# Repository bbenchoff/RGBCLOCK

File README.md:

# RGBCLOCK
RGB Seven-segment clock

On hackaday.io: http://hackaday.io/project/5156-rgb-seven-segment-clock

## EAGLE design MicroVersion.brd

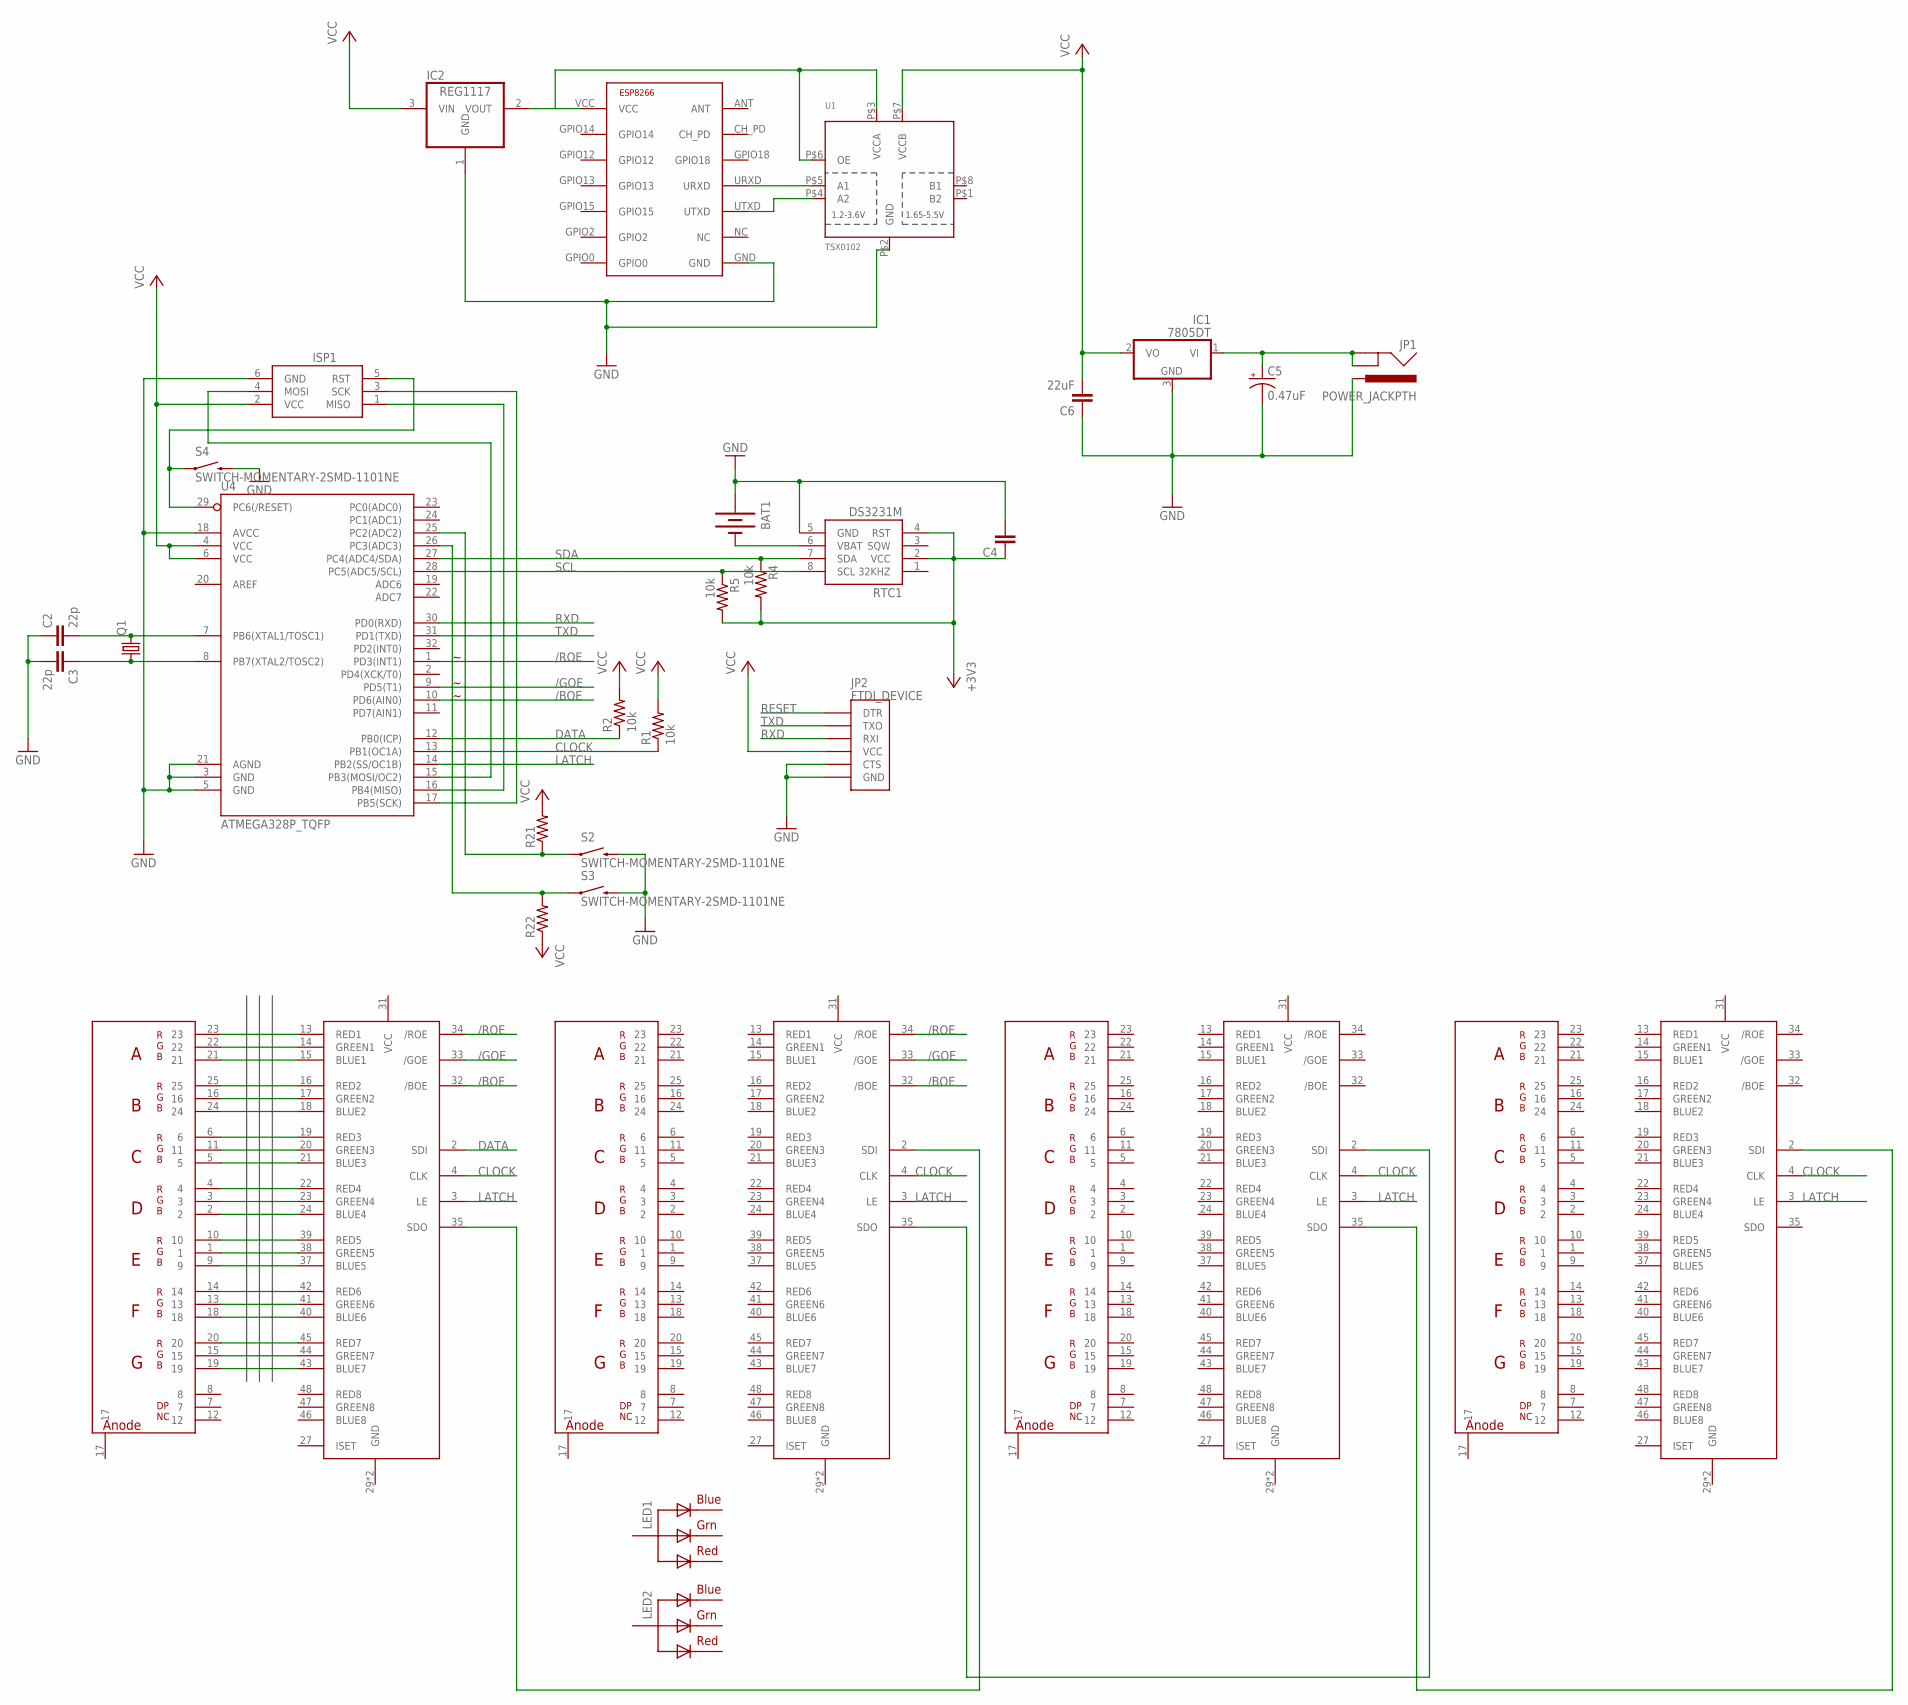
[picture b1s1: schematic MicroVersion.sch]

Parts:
BAT1: BATTERY12MM; BATTCON_12MM
C2, C3: 22p; 0805
C4: CAP0805; 0805
C5: 0.47uF; EIA3216
C6: 22uF; 1210
IC1: 7805DT; TO252
IC2: REG1117; SOT223
ISP1: AVRISP-6; AVRISP
JP1: POWER_JACKPTH; POWER_JACK_PTH
JP2: FTDI_DEVICE; FTDI_DEVICE_SIDE
LED1, LED2: RGBLED_CA-5MM; LED5MMRGB
Q1: CRYSTALCTS406; CTS406
R1, R2, R4, R5: 10k; 0805
R21, R22: RESISTOR0805-RES; 0805
RTC1: DS3231M; SOIC8
S2, S3, S4: SWITCH-MOMENTARY-2SMD-1101NE; TACTILE-SWITCH-1101NE
U1: TSX0102; VFSOP-8
U4: ATMEGA328P_TQFP; TQFP32-08
U$1, U$2, U$3, U$4: RGBSEVENSEGMENT
U$5, U$6, U$7, U$8: LED2472G; TQFP48
U$10: ESP8266-03; ESP-03

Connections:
1BLUE1: U$1.24, U$5.15 (BLUE1)
1BLUE2: U$1.21, U$5.18 (BLUE2)
1BLUE3: U$1.19, U$5.21 (BLUE3)
1BLUE4: U$1.18, U$5.24 (BLUE4)
1BLUE5: U$1.9, U$5.37 (BLUE5)
1BLUE6: U$1.2, U$5.40 (BLUE6)
1BLUE7: U$1.5, U$5.43 (BLUE7)
1GREEN1: U$1.16, U$5.14 (GREEN1)
1GREEN2: U$1.22, U$5.17 (GREEN2)
1GREEN3: U$1.15, U$5.20 (GREEN3)
1GREEN4: U$1.13, U$5.23 (GREEN4)
1GREEN5: U$1.1, U$5.38 (GREEN5)
1GREEN6: U$1.3, U$5.41 (GREEN6)
1GREEN7: U$1.11, U$5.44 (GREEN7)
1RED1: U$1.25, U$5.13 (RED1)
1RED2: U$1.23, U$5.16 (RED2)
1RED3: U$1.20, U$5.19 (RED3)
1RED4: U$1.14, U$5.22 (RED4)
1RED5: U$1.10, U$5.39 (RED5)
1RED6: U$1.4, U$5.42 (RED6)
1RED7: U$1.6, U$5.45 (RED7)
/BOE: U4.10 (PD6(AIN0)), U$5.32 (/BOE), U$6.32 (/BOE)
/GOE: U4.9 (PD5(T1)), U$5.33 (/GOE), U$6.33 (/GOE)
/ROE: U4.1 (PD3(INT1)), U$5.34 (/ROE), U$6.34 (/ROE)
CLOCK: R1.1, U4.13 (PB1(OC1A)), U$5.4 (CLK), U$6.4 (CLK), U$7.4 (CLK), U$8.4 (CLK)
DATA: R2.1, U4.12 (PB0(ICP)), U$5.2 (SDI)
GND: BAT1.PWR@1 (+), C2.1, C3.2, C4.2, C5.C (-), C6.1, IC1.3 (GND), IC2.1 (GND), ISP1.6 (GND), JP1.PWR, JP2.P$5 (CTS), JP2.P$6 (GND), RTC1.5 (GND), S2.2, S3.2, S4.2, U1.P$2 (GND), U4.3 (GND), U4.5 (GND), U4.18 (AVCC), U4.21 (AGND), U$10.GND
LATCH: U4.14 (PB2(SS/OC1B)), U$5.3 (LE), U$6.3 (LE), U$7.3 (LE), U$8.3 (LE)
MISO: ISP1.1 (MISO), U4.16 (PB4(MISO))
MOSI: ISP1.4 (MOSI), U4.15 (PB3(MOSI/OC2))
unnamed: BAT1.GND (-), RTC1.6 (VBAT)
unnamed: U$5.35 (SDO), U$6.2 (SDI)
unnamed: U$6.35 (SDO), U$7.2 (SDI)
unnamed: U$7.35 (SDO), U$8.2 (SDI)
unnamed: C5.A (+), IC1.1 (VI), JP1.GND, JP1.GNDBREAK
unnamed: R22.2, S3.1, U4.26 (PC3(ADC3))
unnamed: R21.1, S2.1, U4.25 (PC2(ADC2))
unnamed: IC2.2 (VOUT), U1.P$3 (VCCA), U1.P$6 (OE), U$10.VCC
unnamed: U1.P$5 (A1), U$10.URXD
unnamed: U1.P$4 (A2), U$10.UTXD
RESET: ISP1.5 (RST), JP2.P$1 (DTR), S4.1, U4.29 (PC6(/RESET))
RXD: JP2.P$3 (RXI), U4.30 (PD0(RXD))
SCK: ISP1.3 (SCK), U4.17 (PB5(SCK))
SCL: R5.1, RTC1.8 (SCL), U4.28 (PC5(ADC5/SCL))
SDA: R4.1, RTC1.7 (SDA), U4.27 (PC4(ADC4/SDA))
TXD: JP2.P$2 (TXO), U4.31 (PD1(TXD))
VCC: C4.1, C6.2, IC1.2 (VO), IC2.3 (VIN), ISP1.2 (VCC), JP2.P$4 (VCC), R1.2, R2.2, R4.2, R5.2, R21.2, R22.1, RTC1.2 (VCC), RTC1.4 (RST), U1.P$7 (VCCB), U4.4 (VCC), U4.6 (VCC)
XTAL1: C2.2, Q1.3 (2), U4.7 (PB6(XTAL1/TOSC1))
XTAL2: C3.1, Q1.1, U4.8 (PB7(XTAL2/TOSC2))

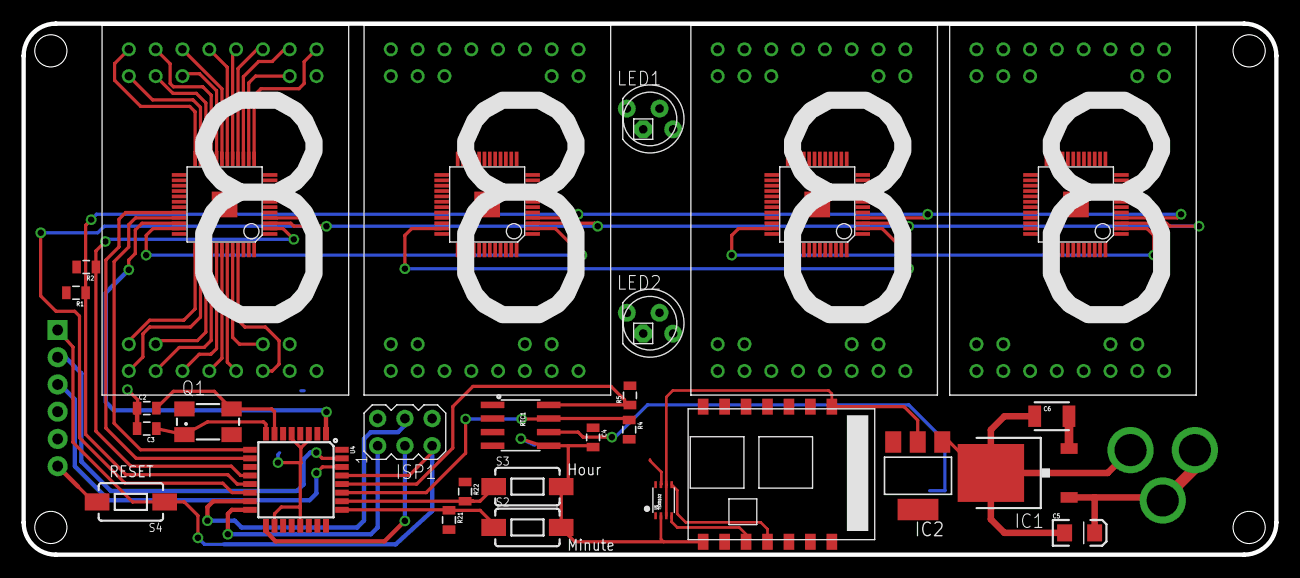
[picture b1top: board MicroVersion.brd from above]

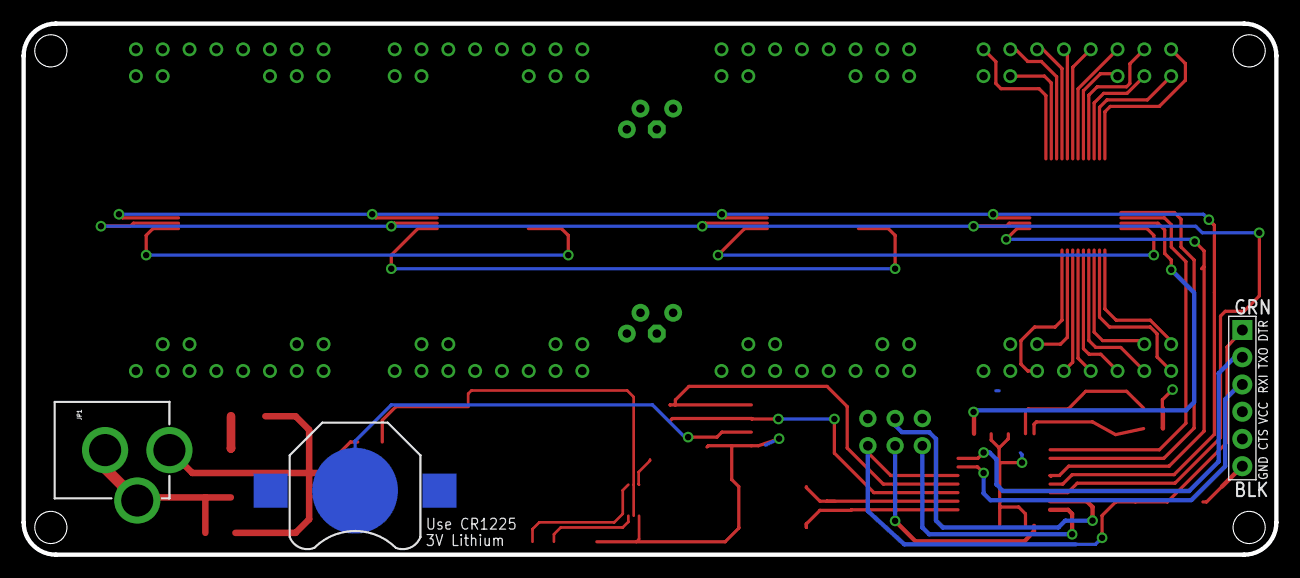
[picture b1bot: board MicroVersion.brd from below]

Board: 2 copper layers, 116.8 x 49.5 mm, 35 parts (3 on the bottom side), 49 nets.

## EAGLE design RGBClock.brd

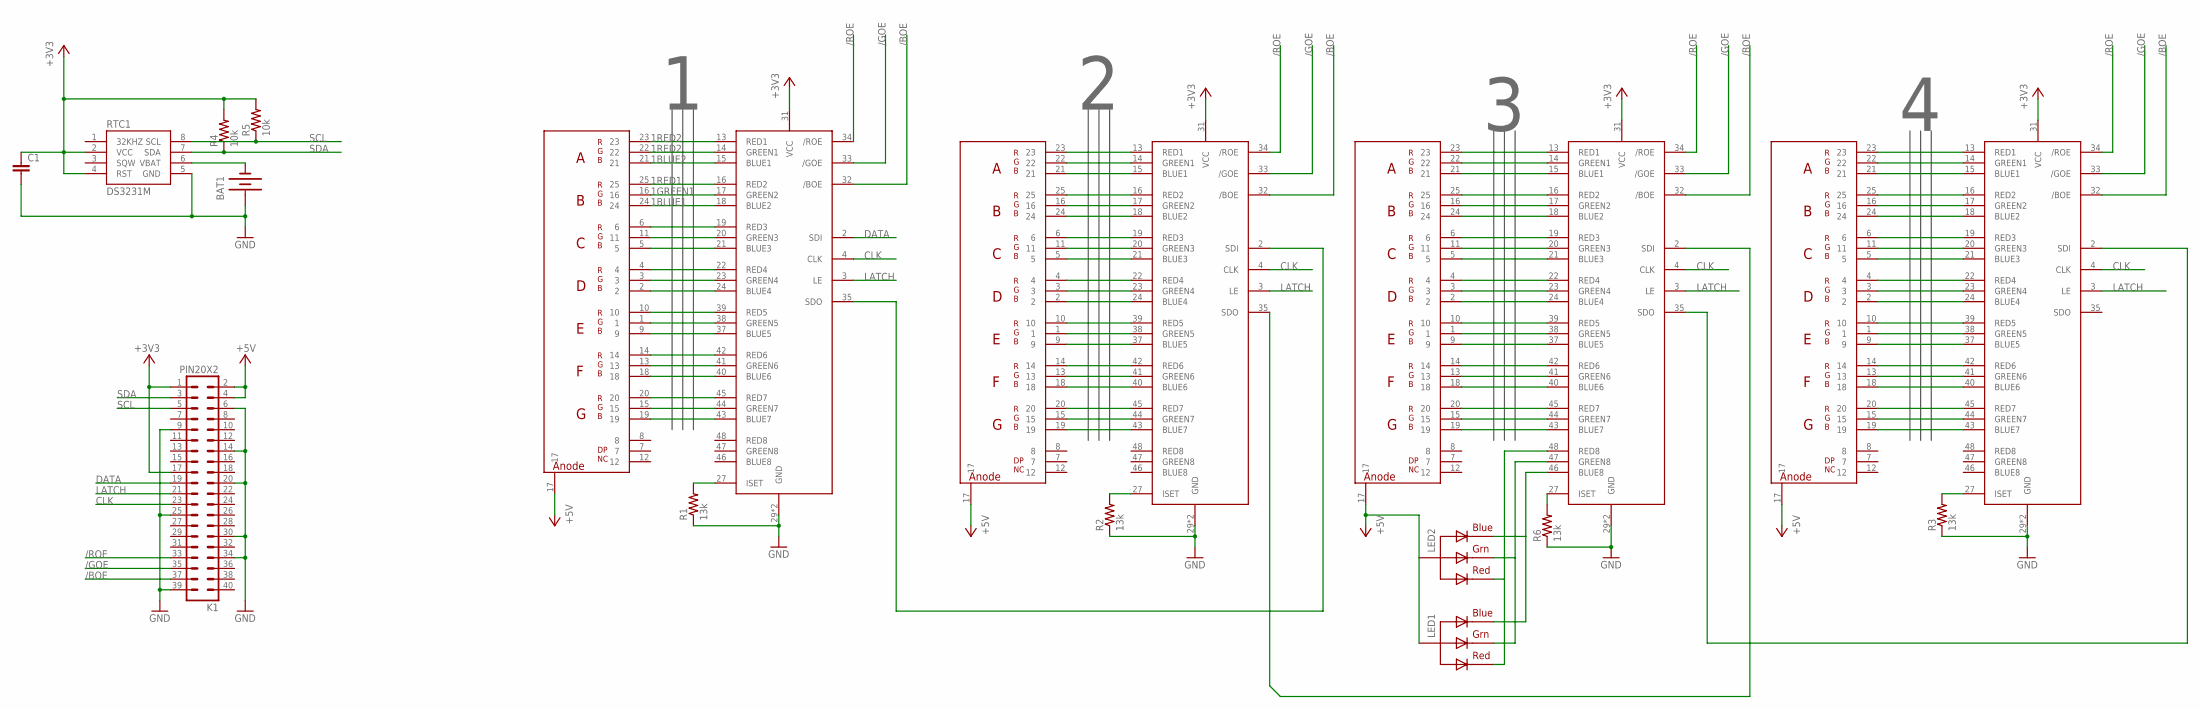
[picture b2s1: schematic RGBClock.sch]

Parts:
BAT1: BATTERY12MM; BATTCON_12MM
C1: CAP0805; 0805
K1: PIN20X2; PIN_20X2
LED1, LED2: RGBLED_CA-5MM; LED5MMRGB
R1, R2, R3, R6: 13k; 0805
R4, R5: 10k; 0805
RTC1: DS3231M; SOIC8
U$2, U$3, U$4, U$5: RGBSEVENSEGMENT
U$6, U$7, U$8, U$9: LED2472G; TQFP48

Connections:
1BLUE1: U$2.24, U$6.15 (BLUE1)
1BLUE2: U$2.21, U$6.18 (BLUE2)
1BLUE3: U$2.19, U$6.21 (BLUE3)
1BLUE4: U$2.18, U$6.24 (BLUE4)
1BLUE5: U$2.9, U$6.37 (BLUE5)
1BLUE6: U$2.2, U$6.40 (BLUE6)
1BLUE7: U$2.5, U$6.43 (BLUE7)
1GREEN1: U$2.16, U$6.14 (GREEN1)
1GREEN2: U$2.22, U$6.17 (GREEN2)
1GREEN3: U$2.15, U$6.20 (GREEN3)
1GREEN4: U$2.13, U$6.23 (GREEN4)
1GREEN5: U$2.1, U$6.38 (GREEN5)
1GREEN6: U$2.3, U$6.41 (GREEN6)
1GREEN7: U$2.11, U$6.44 (GREEN7)
1RED1: U$2.25, U$6.13 (RED1)
1RED2: U$2.23, U$6.16 (RED2)
1RED3: U$2.20, U$6.19 (RED3)
1RED4: U$2.14, U$6.22 (RED4)
1RED5: U$2.10, U$6.39 (RED5)
1RED6: U$2.4, U$6.42 (RED6)
1RED7: U$2.6, U$6.45 (RED7)
2BLUE1: U$3.24, U$7.15 (BLUE1)
2BLUE2: U$3.21, U$7.18 (BLUE2)
2BLUE3: U$3.19, U$7.21 (BLUE3)
2BLUE4: U$3.18, U$7.24 (BLUE4)
2BLUE5: U$3.9, U$7.37 (BLUE5)
2BLUE6: U$3.2, U$7.40 (BLUE6)
2BLUE7: U$3.5, U$7.43 (BLUE7)
2GREEN1: U$3.16, U$7.14 (GREEN1)
2GREEN2: U$3.22, U$7.17 (GREEN2)
2GREEN3: U$3.15, U$7.20 (GREEN3)
2GREEN4: U$3.13, U$7.23 (GREEN4)
2GREEN5: U$3.1, U$7.38 (GREEN5)
2GREEN6: U$3.3, U$7.41 (GREEN6)
2GREEN7: U$3.11, U$7.44 (GREEN7)
2RED1: U$3.25, U$7.13 (RED1)
2RED2: U$3.23, U$7.16 (RED2)
2RED3: U$3.20, U$7.19 (RED3)
2RED4: U$3.14, U$7.22 (RED4)
2RED5: U$3.10, U$7.39 (RED5)
2RED6: U$3.4, U$7.42 (RED6)
2RED7: U$3.6, U$7.45 (RED7)
3BLUE1: U$4.24, U$8.15 (BLUE1)
3BLUE2: U$4.21, U$8.18 (BLUE2)
3BLUE3: U$4.19, U$8.21 (BLUE3)
3BLUE4: U$4.18, U$8.24 (BLUE4)
3BLUE5: U$4.9, U$8.37 (BLUE5)
3BLUE6: U$4.2, U$8.40 (BLUE6)
3BLUE7: U$4.5, U$8.43 (BLUE7)
3GREEN1: U$4.16, U$8.14 (GREEN1)
3GREEN2: U$4.22, U$8.17 (GREEN2)
3GREEN3: U$4.15, U$8.20 (GREEN3)
3GREEN4: U$4.13, U$8.23 (GREEN4)
3GREEN5: U$4.1, U$8.38 (GREEN5)
3GREEN6: U$4.3, U$8.41 (GREEN6)
3GREEN7: U$4.11, U$8.44 (GREEN7)
3RED1: U$4.25, U$8.13 (RED1)
3RED2: U$4.23, U$8.16 (RED2)
3RED3: U$4.20, U$8.19 (RED3)
3RED4: U$4.14, U$8.22 (RED4)
3RED5: U$4.10, U$8.39 (RED5)
3RED6: U$4.4, U$8.42 (RED6)
3RED7: U$4.6, U$8.45 (RED7)
4BLUE1: U$5.24, U$9.15 (BLUE1)
4BLUE2: U$5.21, U$9.18 (BLUE2)
4BLUE3: U$5.19, U$9.21 (BLUE3)
4BLUE4: U$5.18, U$9.24 (BLUE4)
4BLUE5: U$5.9, U$9.37 (BLUE5)
4BLUE6: U$5.2, U$9.40 (BLUE6)
4BLUE7: U$5.5, U$9.43 (BLUE7)
4GREEN1: U$5.16, U$9.14 (GREEN1)
4GREEN2: U$5.22, U$9.17 (GREEN2)
4GREEN3: U$5.15, U$9.20 (GREEN3)
4GREEN4: U$5.13, U$9.23 (GREEN4)
4GREEN5: U$5.1, U$9.38 (GREEN5)
4GREEN6: U$5.3, U$9.41 (GREEN6)
4GREEN7: U$5.11, U$9.44 (GREEN7)
4RED1: U$5.25, U$9.13 (RED1)
4RED2: U$5.23, U$9.16 (RED2)
4RED3: U$5.20, U$9.19 (RED3)
4RED4: U$5.14, U$9.22 (RED4)
4RED5: U$5.10, U$9.39 (RED5)
4RED6: U$5.4, U$9.42 (RED6)
4RED7: U$5.6, U$9.45 (RED7)
+3V3: C1.1, K1.1, K1.17, R4.2, R5.2, RTC1.2 (VCC), RTC1.4 (RST), U$6.31 (VCC), U$7.31 (VCC), U$8.31 (VCC), U$9.31 (VCC)
+5V: K1.2, K1.4, LED1.2 (VCC), LED2.2 (VCC), U$2.17, U$3.17, U$4.17, U$5.17
/BOE: K1.37, U$6.32 (/BOE), U$7.32 (/BOE), U$8.32 (/BOE), U$9.32 (/BOE)
/GOE: K1.35, U$6.33 (/GOE), U$7.33 (/GOE), U$8.33 (/GOE), U$9.33 (/GOE)
/ROE: K1.33, U$6.34 (/ROE), U$7.34 (/ROE), U$8.34 (/ROE), U$9.34 (/ROE)
CLK: K1.23, U$6.4 (CLK), U$7.4 (CLK), U$8.4 (CLK), U$9.4 (CLK)
DATA: K1.19, U$6.2 (SDI)
GND: BAT1.PWR@1 (+), C1.2, K1.6, K1.9, K1.14, K1.20, K1.25, K1.30, K1.34, K1.39, R1.1, R2.1, R3.1, R6.1, RTC1.5 (GND), U$6.29 (GND), U$6.30 (GND), U$7.29 (GND), U$7.30 (GND), U$8.29 (GND), U$8.30 (GND), U$9.29 (GND), U$9.30 (GND)
LATCH: K1.21, U$6.3 (LE), U$7.3 (LE), U$8.3 (LE), U$9.3 (LE)
unnamed: BAT1.GND (-), RTC1.6 (VBAT)
unnamed: LED1.1 (RED), LED2.1 (RED), U$8.48 (RED8)
unnamed: LED1.4 (BLUE), LED2.4 (BLUE), U$8.46 (BLUE8)
unnamed: LED1.3 (GREEN), LED2.3 (GREEN), U$8.47 (GREEN8)
unnamed: R6.2, U$8.27 (ISET)
unnamed: R3.2, U$9.27 (ISET)
unnamed: R2.2, U$7.27 (ISET)
unnamed: R1.2, U$6.27 (ISET)
unnamed: U$6.35 (SDO), U$7.2 (SDI)
unnamed: U$7.35 (SDO), U$8.2 (SDI)
unnamed: U$8.35 (SDO), U$9.2 (SDI)
SCL: K1.5, R5.1, RTC1.8 (SCL)
SDA: K1.3, R4.1, RTC1.7 (SDA)

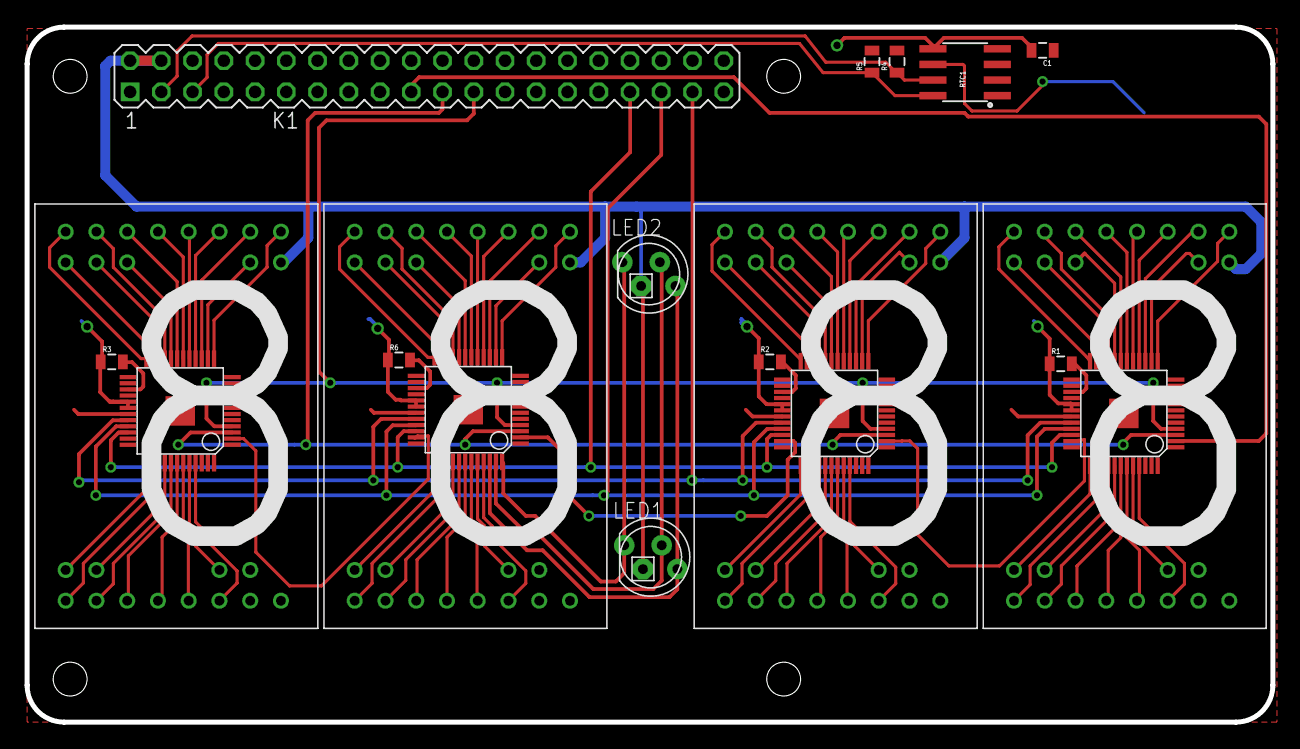
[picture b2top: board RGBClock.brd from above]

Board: 2 copper layers, 101.3 x 56.5 mm, 20 parts (1 on the bottom side), 106 nets.

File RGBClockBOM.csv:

Qty,Value,Device,Package,Parts,Description,Manufacturer,Manufacturer_ID,Mouser,Digikey,Adafruit
,,,,,,,,,,
1,,BATTERY12MM,BATTCON_12MM,BAT1,Battery Holders,Keystone,3080,http://www.mouser.com/ProductDetail/Keystone-Electronics/3080/,,
1,DS3231M,DS3231M,SOIC8,RTC1,DS3231M Real Time Clock.  Accuracy +/-5ppm.  Battery Backup.  2.3V to 5.5V.,Maxim,DS3231MZ+,http://www.mouser.com/ProductDetail/Maxim-Integrated/DS3231M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,,
4,LED2472G,LED2472G,TQFP48,"U$6, U$7, U$8, U$9",,ST,LED2472GBTR,http://www.mouser.com/ProductDetail/STMicroelectronics/LED24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,,
2,RGBLED_CA-5MM,RGBLED_CA-5MM,LED5MMRGB,"LED1, LED2","RGB LED, common-anode5MM Staggered pins5mm Piranha package",,,,,
4,RGBSEVENSEGMENT,RGBSEVENSEGMENT,RGBSEVENSEGMENT,"U$2, U$3, U$4, U$5",Single digit seven-segment RGB LED display,A'SYCK,AD-121F2,,,http://www.adafruit.com/products/1399
,,,,,,,,,,
1,,CAP0805,805,C1,Capacitor,,,,,
2,10k,RESISTOR0805-RES,805,"R4, R5",Resistor,,,,,
4,13k,RESISTOR0805-RES,805,"R1, R2, R3, R6",Resistor,,,,,
1,PIN20X2,PIN20X2,PIN_20X2,K1,,,,,,http://www.adafruit.com/products/1992

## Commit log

2015-04-07 :neckbeard: Added .gitattributes & .gitignore files
2015-04-08 Finished board
2015-04-08 Board, gerbers, and BOM
2015-04-08 Unimportant changes
2015-04-08 Added Beginning of Microcontroller version
2015-04-10 More microcontroller version
2015-04-12 Huge update to micro version
2015-04-26 Deleted useless stuff
2015-04-26 printable schematic

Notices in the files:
parts and their libraries:
SparkFun-Passives: Licensing: Creative Commons ShareAlike 4.0 International - https://creativecommons.org/licenses/by-sa/4.0
